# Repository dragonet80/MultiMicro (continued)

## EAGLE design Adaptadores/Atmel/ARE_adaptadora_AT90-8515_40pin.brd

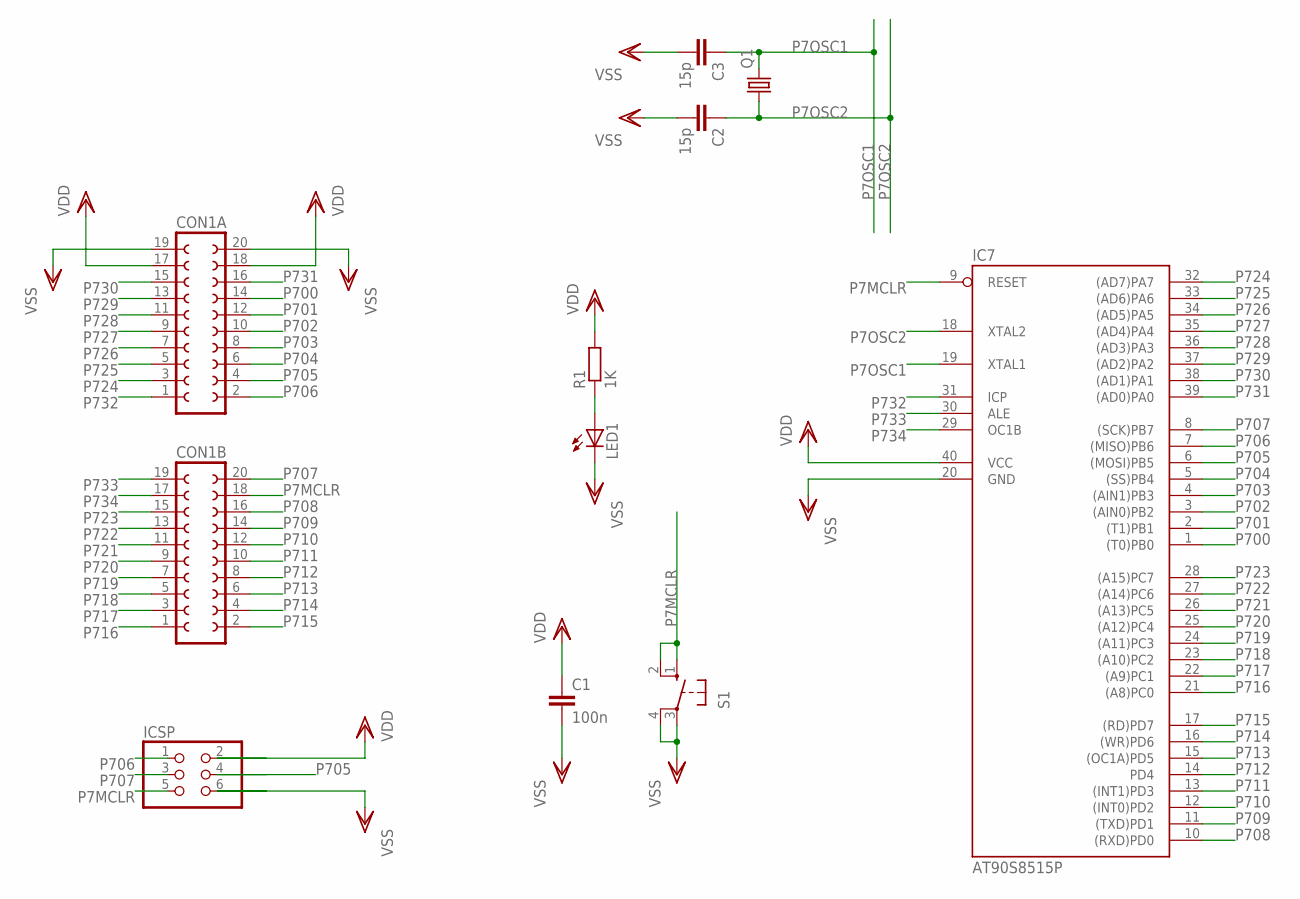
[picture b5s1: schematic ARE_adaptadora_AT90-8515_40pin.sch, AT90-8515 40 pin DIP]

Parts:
C1: 100n; C0805
C2, C3: 15p; C0805
CON1A, CON1B: FE10-2W
IC7: AT90S8515P; DIL40
ICSP: PINHD-2X3; 2X03
LED1: LED3MM
Q1: CRYSTALHC18U-V; HC18U-V
R1: 1K; R0805
S1: 10-XX; B3F-10XX; MPN B3F-1000

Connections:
unnamed: LED1.A, R1.1
P7MCLR: CON1B.18, IC7.9 (RESET), ICSP.5, S1.1 (S), S1.2 (S1)
P7OSC1: C3.1, IC7.19 (XTAL1), Q1.2
P7OSC2: C2.1, IC7.18 (XTAL2), Q1.1
P700: CON1A.14, IC7.1 ((T0)PB0)
P701: CON1A.12, IC7.2 ((T1)PB1)
P702: CON1A.10, IC7.3 ((AIN0)PB2)
P703: CON1A.8, IC7.4 ((AIN1)PB3)
P704: CON1A.6, IC7.5 ((SS)PB4)
P705: CON1A.4, IC7.6 ((MOSI)PB5), ICSP.4
P706: CON1A.2, IC7.7 ((MISO)PB6), ICSP.1
P707: CON1B.20, IC7.8 ((SCK)PB7), ICSP.3
P708: CON1B.16, IC7.10 ((RXD)PD0)
P709: CON1B.14, IC7.11 ((TXD)PD1)
P710: CON1B.12, IC7.12 ((INT0)PD2)
P711: CON1B.10, IC7.13 ((INT1)PD3)
P712: CON1B.8, IC7.14 (PD4)
P713: CON1B.6, IC7.15 ((OC1A)PD5)
P714: CON1B.4, IC7.16 ((WR)PD6)
P715: CON1B.2, IC7.17 ((RD)PD7)
P716: CON1B.1, IC7.21 ((A8)PC0)
P717: CON1B.3, IC7.22 ((A9)PC1)
P718: CON1B.5, IC7.23 ((A10)PC2)
P719: CON1B.7, IC7.24 ((A11)PC3)
P720: CON1B.9, IC7.25 ((A12)PC4)
P721: CON1B.11, IC7.26 ((A13)PC5)
P722: CON1B.13, IC7.27 ((A14)PC6)
P723: CON1B.15, IC7.28 ((A15)PC7)
P724: CON1A.3, IC7.32 ((AD7)PA7)
P725: CON1A.5, IC7.33 ((AD6)PA6)
P726: CON1A.7, IC7.34 ((AD5)PA5)
P727: CON1A.9, IC7.35 ((AD4)PA4)
P728: CON1A.11, IC7.36 ((AD3)PA3)
P729: CON1A.13, IC7.37 ((AD2)PA2)
P730: CON1A.15, IC7.38 ((AD1)PA1)
P731: CON1A.16, IC7.39 ((AD0)PA0)
P732: CON1A.1, IC7.31 (ICP)
P733: CON1B.19, IC7.30 (ALE)
P734: CON1B.17, IC7.29 (OC1B)
VDD: C1.1, CON1A.17, CON1A.18, IC7.40 (VCC), ICSP.2, R1.2
VSS: C1.2, C2.2, C3.2, CON1A.19, CON1A.20, IC7.20 (GND), ICSP.6, LED1.K (C), S1.3, S1.4 (P1)

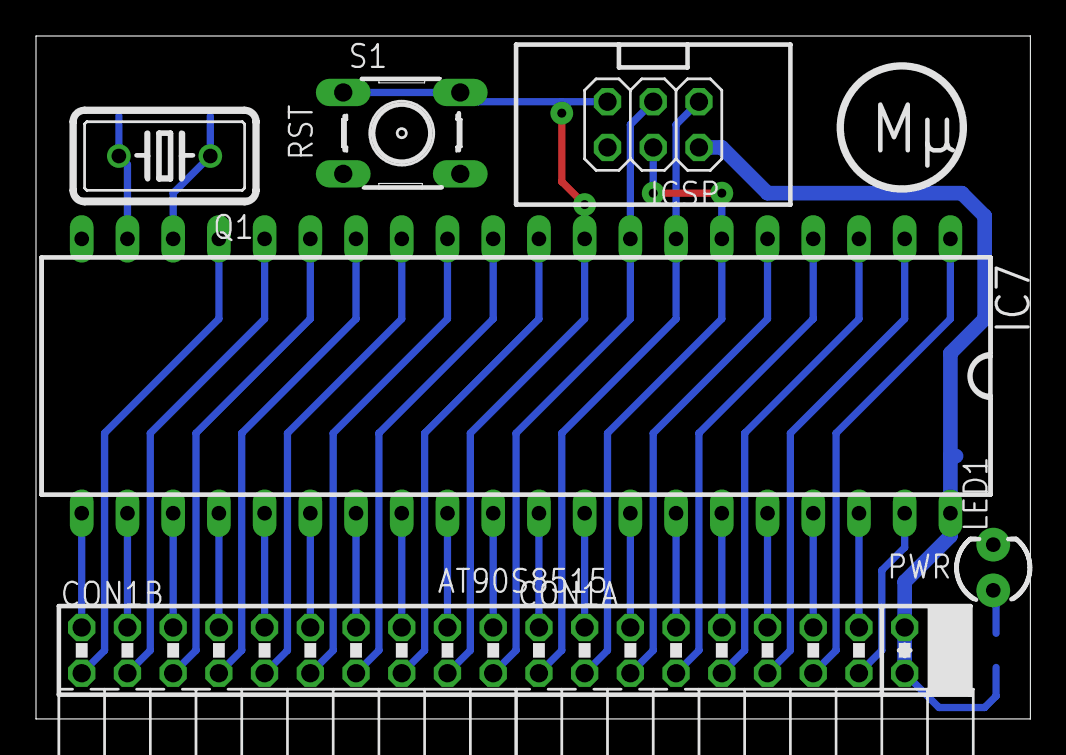
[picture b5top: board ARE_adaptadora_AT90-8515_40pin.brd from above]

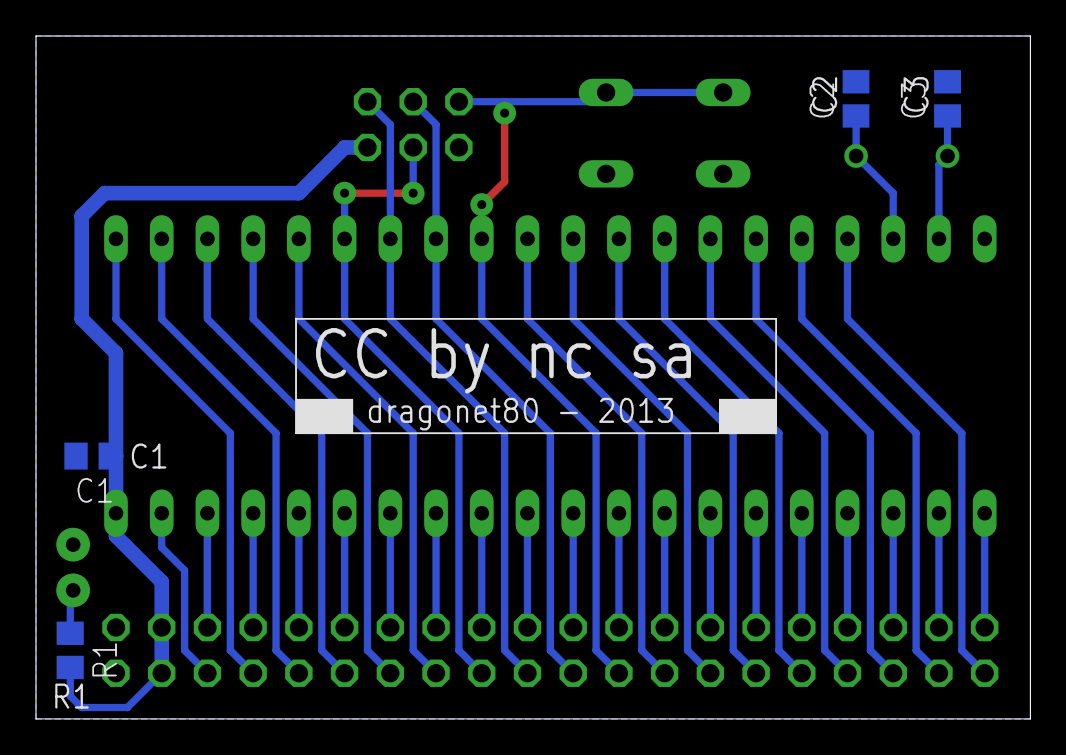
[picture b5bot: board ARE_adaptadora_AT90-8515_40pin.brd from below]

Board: 2 copper layers, 55.2 x 37.9 mm, 11 parts (4 on the bottom side), 41 nets.

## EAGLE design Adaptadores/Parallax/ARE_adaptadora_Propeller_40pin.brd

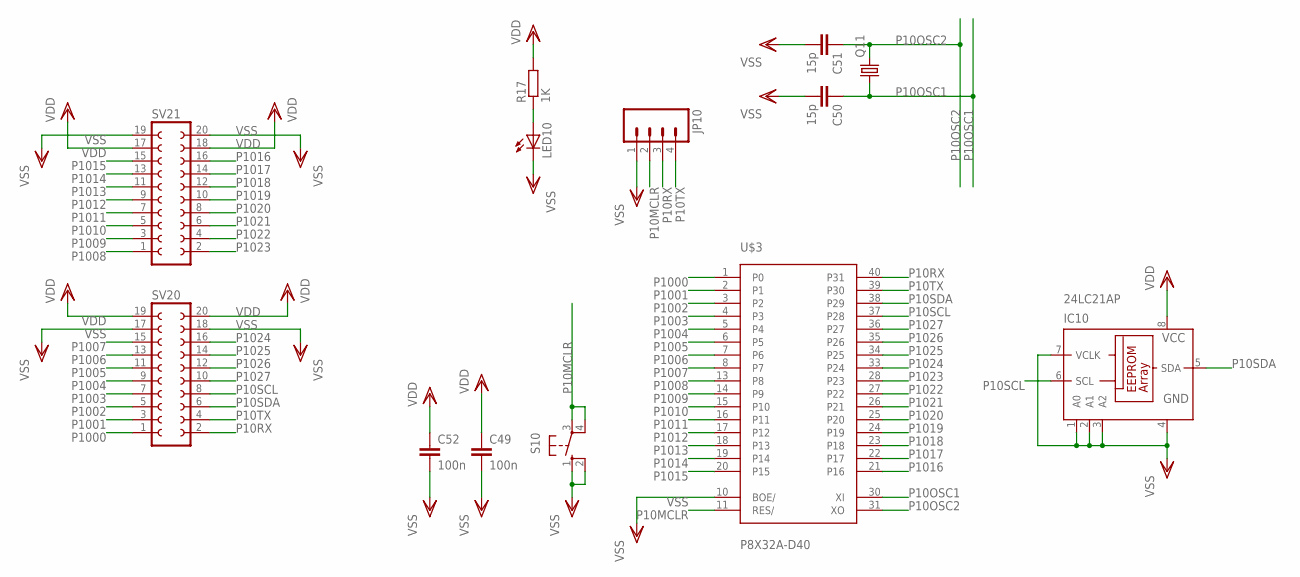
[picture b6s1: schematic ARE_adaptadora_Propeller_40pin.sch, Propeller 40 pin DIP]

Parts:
C49, C52: 100n; C0805
C50, C51: 15p; C0805
IC10: 24LC21AP; DIL8
JP10: M04PTH; 1X04
LED10: LED3MM
Q11: CRYSTALHC18U-V; HC18U-V
R17: 1K; R0805
S10: 10-XX; B3F-10XX; MPN B3F-1000
SV20, SV21: FE10-2W
U$3: P8X32A-D40

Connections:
unnamed: LED10.A, R17.1
P10MCLR: JP10.2, S10.3, S10.4 (P1), U$3.11 (RES/)
P10OSC1: C50.1, Q11.1, U$3.30 (XI)
P10OSC2: C51.1, Q11.2, U$3.31 (XO)
P10RX: JP10.3, SV20.2, U$3.40 (P31)
P10SCL: IC10.6 (SCL), SV20.8, U$3.37 (P28)
P10SDA: IC10.5 (SDA), SV20.6, U$3.38 (P29)
P10TX: JP10.4, SV20.4, U$3.39 (P30)
P1000: SV20.1, U$3.1 (P0)
P1001: SV20.3, U$3.2 (P1)
P1002: SV20.5, U$3.3 (P2)
P1003: SV20.7, U$3.4 (P3)
P1004: SV20.9, U$3.5 (P4)
P1005: SV20.11, U$3.6 (P5)
P1006: SV20.13, U$3.7 (P6)
P1007: SV20.15, U$3.8 (P7)
P1008: SV21.1, U$3.13 (P8)
P1009: SV21.3, U$3.14 (P9)
P1010: SV21.5, U$3.15 (P10)
P1011: SV21.7, U$3.16 (P11)
P1012: SV21.9, U$3.17 (P12)
P1013: SV21.11, U$3.18 (P13)
P1014: SV21.13, U$3.19 (P14)
P1015: SV21.15, U$3.20 (P15)
P1016: SV21.16, U$3.21 (P16)
P1017: SV21.14, U$3.22 (P17)
P1018: SV21.12, U$3.23 (P18)
P1019: SV21.10, U$3.24 (P19)
P1020: SV21.8, U$3.25 (P20)
P1021: SV21.6, U$3.26 (P21)
P1022: SV21.4, U$3.27 (P22)
P1023: SV21.2, U$3.28 (P23)
P1024: SV20.16, U$3.33 (P24)
P1025: SV20.14, U$3.34 (P25)
P1026: SV20.12, U$3.35 (P26)
P1027: SV20.10, U$3.36 (P27)
VDD: C49.1, C52.1, IC10.8 (VCC), R17.2, SV20.19, SV20.20, SV21.17, SV21.18, U$3.12 (VDD), U$3.32 (VDD)
VSS: C49.2, C50.2, C51.2, C52.2, IC10.1 (A0), IC10.2 (A1), IC10.3 (A2), IC10.4 (GND), IC10.7 (VCLK), JP10.1, LED10.K (C), S10.1 (S), S10.2 (S1), SV20.17, SV20.18, SV21.19, SV21.20, U$3.9 (VSS), U$3.10 (BOE/), U$3.29 (VSS)

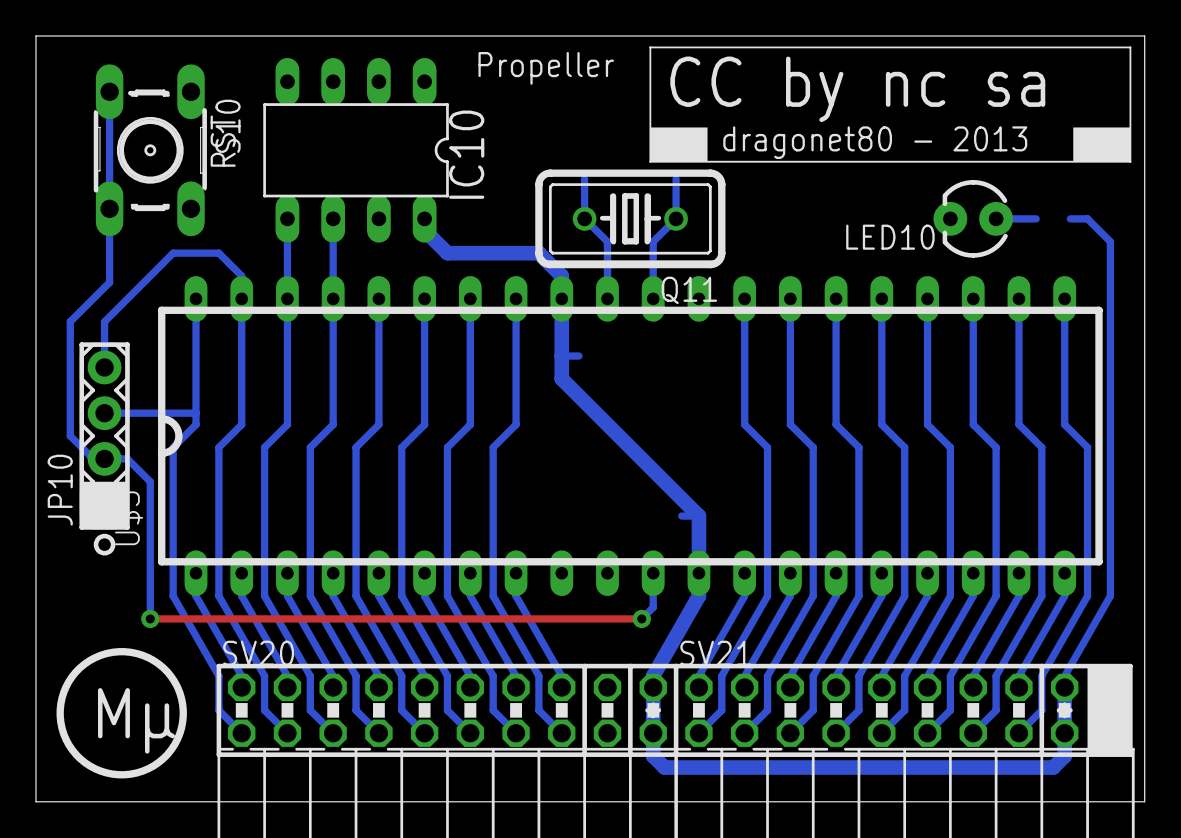
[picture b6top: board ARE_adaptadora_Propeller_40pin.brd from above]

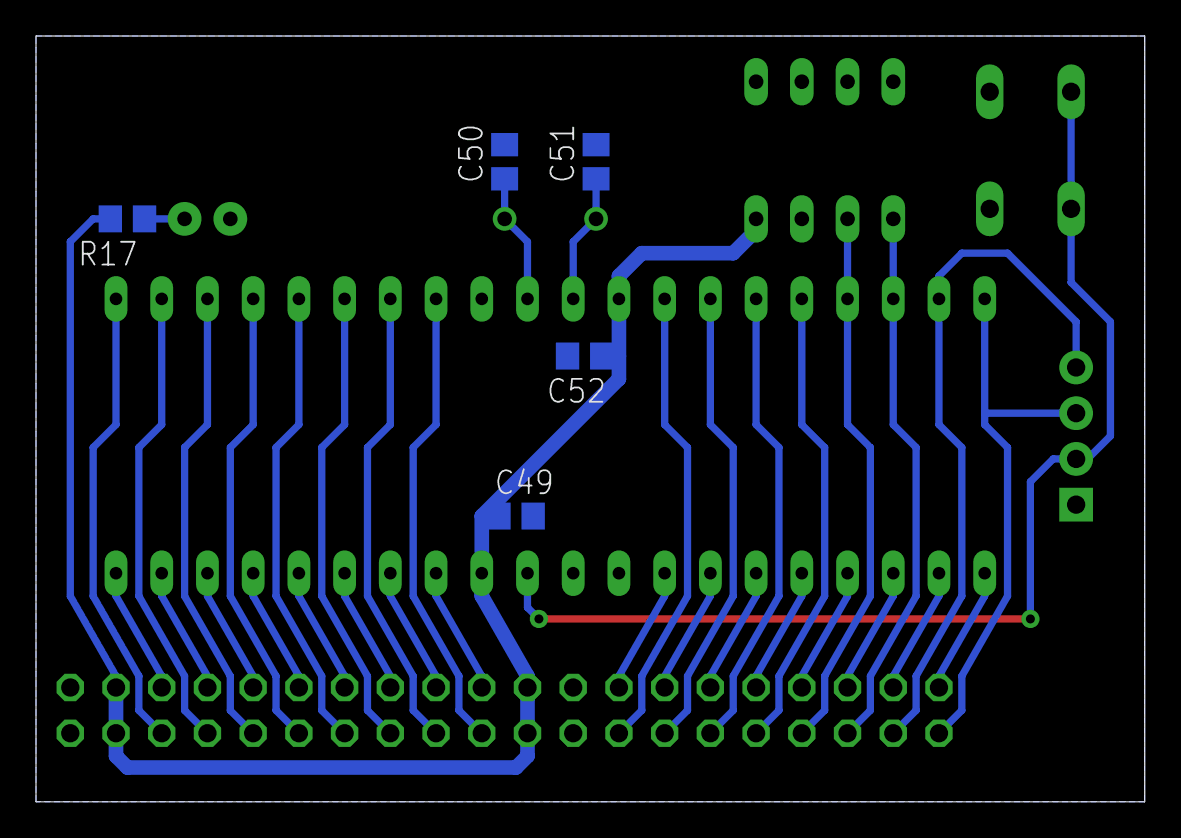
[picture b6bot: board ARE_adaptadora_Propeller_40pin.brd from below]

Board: 2 copper layers, 61.6 x 42.5 mm, 13 parts (5 on the bottom side), 38 nets.

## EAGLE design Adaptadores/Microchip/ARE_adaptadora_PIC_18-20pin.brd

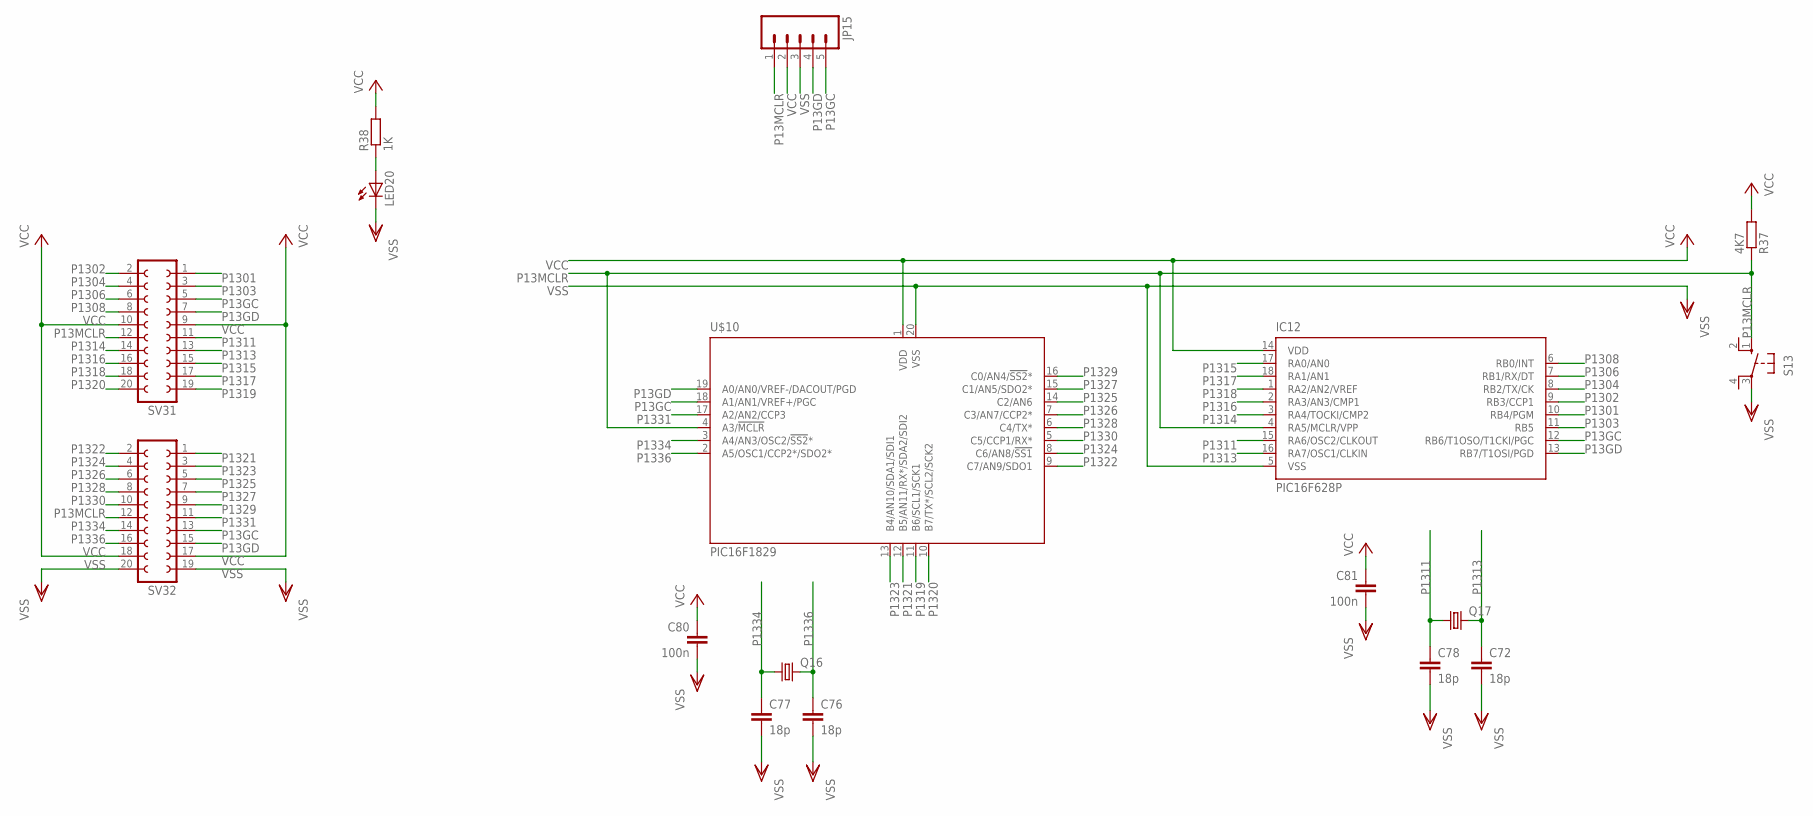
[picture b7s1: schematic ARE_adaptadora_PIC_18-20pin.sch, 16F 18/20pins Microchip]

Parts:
C72, C76, C77, C78: 18p; C0805
C80, C81: 100n; C0805
IC12: PIC16F628P; DIL18
JP15: M05PTH; 1X05
LED20: LEDCHIPLED_0805; CHIPLED_0805
Q16, Q17: CRYSTALHC18U-V; HC18U-V
R37: 4K7; R0805
R38: 1K; R0805
S13: 10-XX; B3F-10XX; MPN B3F-1000
SV31, SV32: FE10-2W
U$10: PIC16F1829; DIL20

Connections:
unnamed: LED20.A, R38.1
P13GC: IC12.12 (RB6/T1OSO/T1CKI/PGC), JP15.5, SV31.5, SV32.13, U$10.18 (A1/AN1/VREF+/PGC)
P13GD: IC12.13 (RB7/T1OSI/PGD), JP15.4, SV31.7, SV32.15, U$10.19 (A0/AN0/VREF-/DACOUT/PGD)
P13MCLR: IC12.4 (RA5/MCLR/VPP), JP15.1, R37.1, S13.1 (S), SV31.12, SV32.12, U$10.4 (A3/!MCLR)
P1301: IC12.10 (RB4/PGM), SV31.1
P1302: IC12.9 (RB3/CCP1), SV31.2
P1303: IC12.11 (RB5), SV31.3
P1304: IC12.8 (RB2/TX/CK), SV31.4
P1306: IC12.7 (RB1/RX/DT), SV31.6
P1308: IC12.6 (RB0/INT), SV31.8
P1311: C78.1, IC12.15 (RA6/OSC2/CLKOUT), Q17.1, SV31.11
P1313: C72.1, IC12.16 (RA7/OSC1/CLKIN), Q17.2, SV31.13
P1314: IC12.3 (RA4/TOCKI/CMP2), SV31.14
P1315: IC12.17 (RA0/AN0), SV31.15
P1316: IC12.2 (RA3/AN3/CMP1), SV31.16
P1317: IC12.18 (RA1/AN1), SV31.17
P1318: IC12.1 (RA2/AN2/VREF), SV31.18
P1319: SV31.19, U$10.11 (B6/SCL1/SCK1)
P1320: SV31.20, U$10.10 (B7/TX*/SCL2/SCK2)
P1321: SV32.1, U$10.12 (B5/AN11/RX*/SDA2/SDI2)
P1322: SV32.2, U$10.9 (C7/AN9/SDO1)
P1323: SV32.3, U$10.13 (B4/AN10/SDA1/SDI1)
P1324: SV32.4, U$10.8 (C6/AN8/!SS1)
P1325: SV32.5, U$10.14 (C2/AN6)
P1326: SV32.6, U$10.7 (C3/AN7/CCP2*)
P1327: SV32.7, U$10.15 (C1/AN5/SDO2*)
P1328: SV32.8, U$10.6 (C4/TX*)
P1329: SV32.9, U$10.16 (C0/AN4/!SS2!*)
P1330: SV32.10, U$10.5 (C5/CCP1/RX*)
P1331: SV32.11, U$10.17 (A2/AN2/CCP3)
P1334: C77.1, Q16.1, SV32.14, U$10.3 (A4/AN3/OSC2/!SS2!*)
P1336: C76.1, Q16.2, SV32.16, U$10.2 (A5/OSC1/CCP2*/SDO2*)
VCC: C80.1, C81.1, IC12.14 (VDD), JP15.2, R37.2, R38.2, SV31.9, SV31.10, SV32.17, SV32.18, U$10.1 (VDD)
VSS: C72.2, C76.2, C77.2, C78.2, C80.2, C81.2, IC12.5 (VSS), JP15.3, LED20.C, S13.3, SV32.19, SV32.20, U$10.20 (VSS)

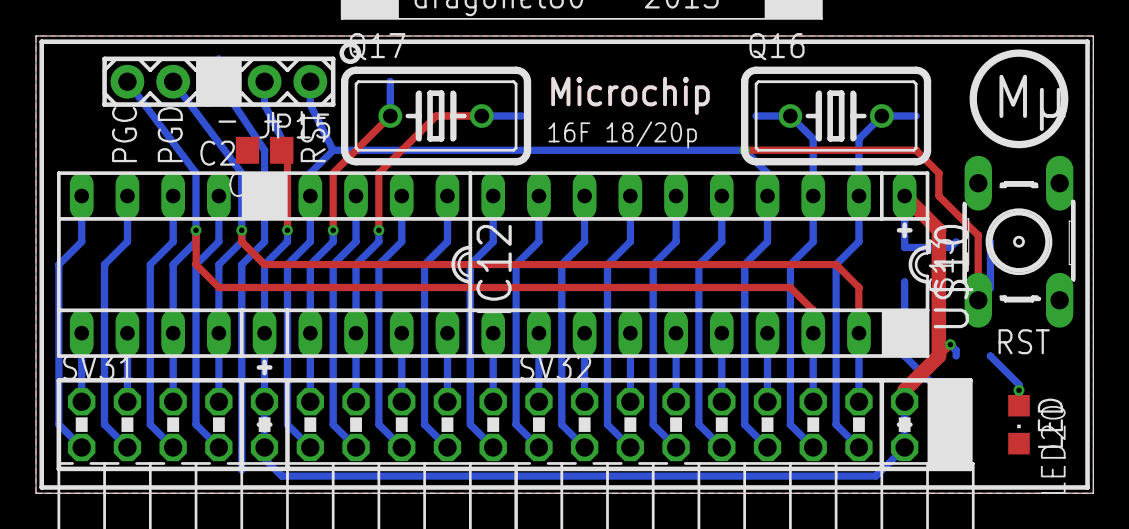
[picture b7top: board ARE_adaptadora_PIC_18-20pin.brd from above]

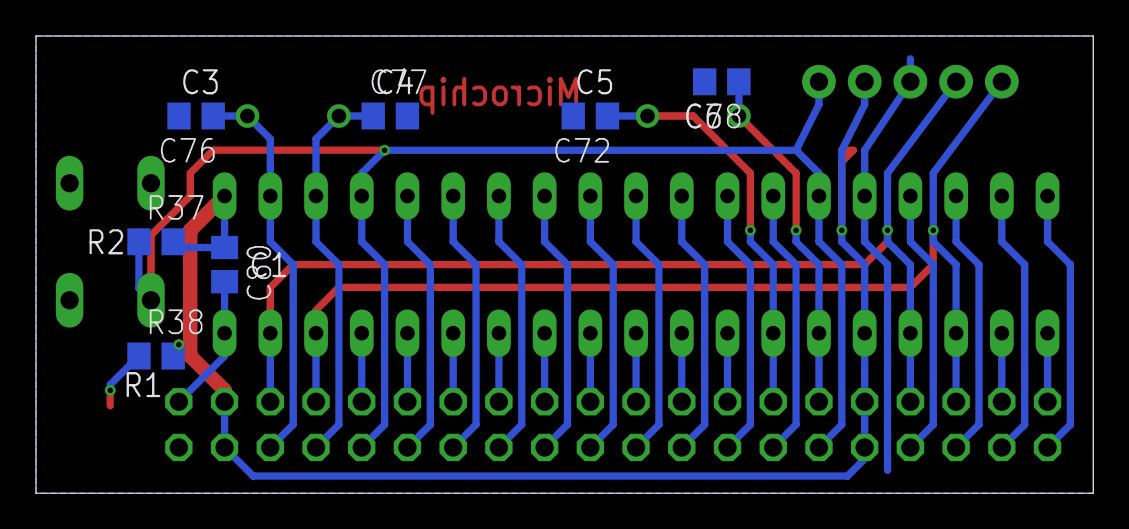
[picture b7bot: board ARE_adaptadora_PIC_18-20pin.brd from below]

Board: 2 copper layers, 58.7 x 25.4 mm, 17 parts (7 on the bottom side), 34 nets.

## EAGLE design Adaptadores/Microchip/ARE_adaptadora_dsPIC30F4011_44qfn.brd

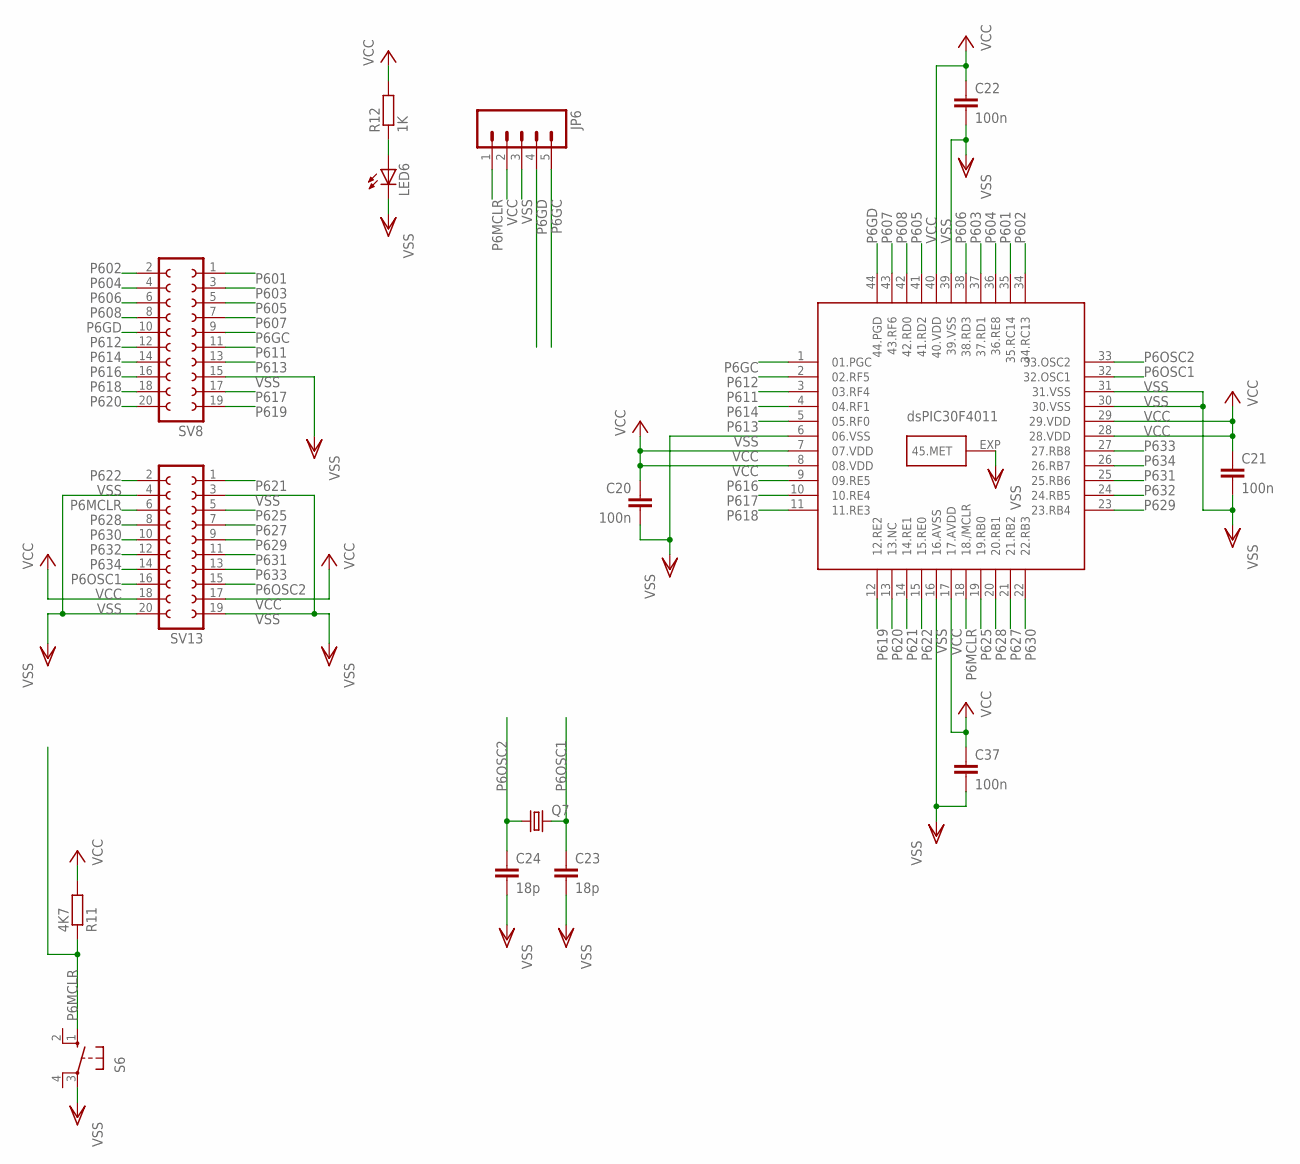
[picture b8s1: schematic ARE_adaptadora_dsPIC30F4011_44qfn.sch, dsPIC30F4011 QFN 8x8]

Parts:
C20, C21, C22, C37: 100n; C0805
C23, C24: 18p; C0805
JP6: M05PTH; 1X05
LED6: LEDCHIPLED_0805; CHIPLED_0805
Q7: CRYSTALHC18U-V; HC18U-V
R11: 4K7; R0805
R12: 1K; R0805
S6: 10-XX; B3F-10XX; MPN B3F-1000
SV8, SV13: FE10-2W
U$2: DSPIC30F4011; QFN44ML8X8

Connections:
unnamed: LED6.A, R12.1
P6GC: JP6.5, SV8.9, U$2.1 (01.PGC)
P6GD: JP6.4, SV8.10, U$2.44 (44.PGD)
P6MCLR: JP6.1, R11.1, S6.1 (S), SV13.6, U$2.18 (18./MCLR)
P6OSC1: C23.1, Q7.2, SV13.16, U$2.32 (32.OSC1)
P6OSC2: C24.1, Q7.1, SV13.15, U$2.33 (33.OSC2)
P601: SV8.1, U$2.35 (35.RC14)
P602: SV8.2, U$2.34 (34.RC13)
P603: SV8.3, U$2.37 (37.RD1)
P604: SV8.4, U$2.36 (36.RE8)
P605: SV8.5, U$2.41 (41.RD2)
P606: SV8.6, U$2.38 (38.RD3)
P607: SV8.7, U$2.43 (43.RF6)
P608: SV8.8, U$2.42 (42.RD0)
P611: SV8.11, U$2.3 (03.RF4)
P612: SV8.12, U$2.2 (02.RF5)
P613: SV8.13, U$2.5 (05.RF0)
P614: SV8.14, U$2.4 (04.RF1)
P616: SV8.16, U$2.9 (09.RE5)
P617: SV8.17, U$2.10 (10.RE4)
P618: SV8.18, U$2.11 (11.RE3)
P619: SV8.19, U$2.12 (12.RE2)
P620: SV8.20, U$2.13 (13.NC)
P621: SV13.1, U$2.14 (14.RE1)
P622: SV13.2, U$2.15 (15.RE0)
P625: SV13.5, U$2.19 (19.RB0)
P627: SV13.7, U$2.21 (21.RB2)
P628: SV13.8, U$2.20 (20.RB1)
P629: SV13.9, U$2.23 (23.RB4)
P630: SV13.10, U$2.22 (22.RB3)
P631: SV13.11, U$2.25 (25.RB6)
P632: SV13.12, U$2.24 (24.RB5)
P633: SV13.13, U$2.27 (27.RB8)
P634: SV13.14, U$2.26 (26.RB7)
VCC: C20.1, C21.1, C22.1, C37.1, JP6.2, R11.2, R12.2, SV13.17, SV13.18, U$2.7 (07.VDD), U$2.8 (08.VDD), U$2.17 (17.AVDD), U$2.28 (28.VDD), U$2.29 (29.VDD), U$2.40 (40.VDD)
VSS: C20.2, C21.2, C22.2, C23.2, C24.2, C37.2, JP6.3, LED6.C, S6.3, SV8.15, SV13.3, SV13.4, SV13.19, SV13.20, U$2.6 (06.VSS), U$2.16 (16.AVSS), U$2.30 (30.VSS), U$2.31 (31.VSS), U$2.39 (39.VSS), U$2.EXP (45.MET)

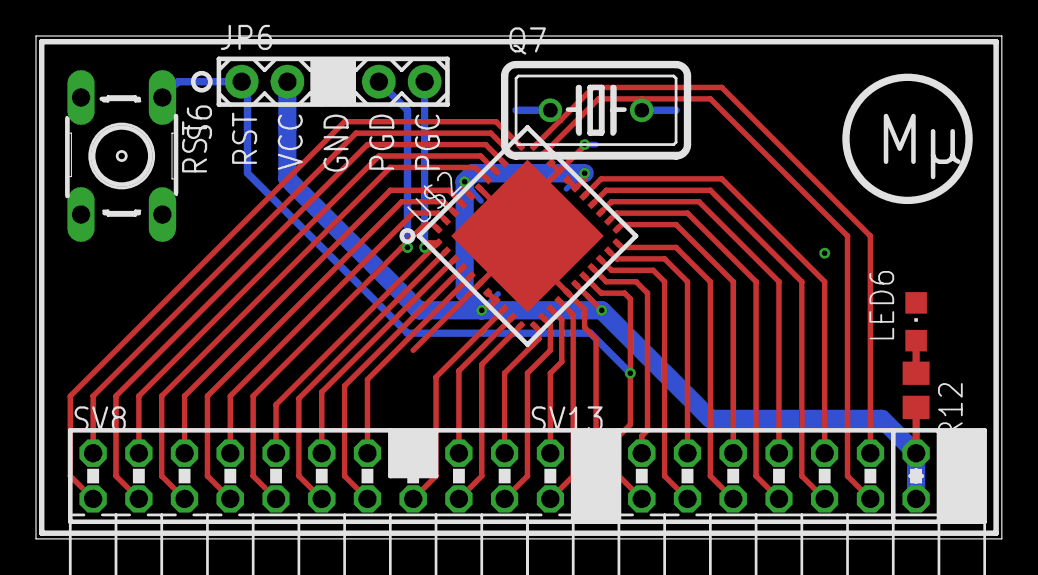
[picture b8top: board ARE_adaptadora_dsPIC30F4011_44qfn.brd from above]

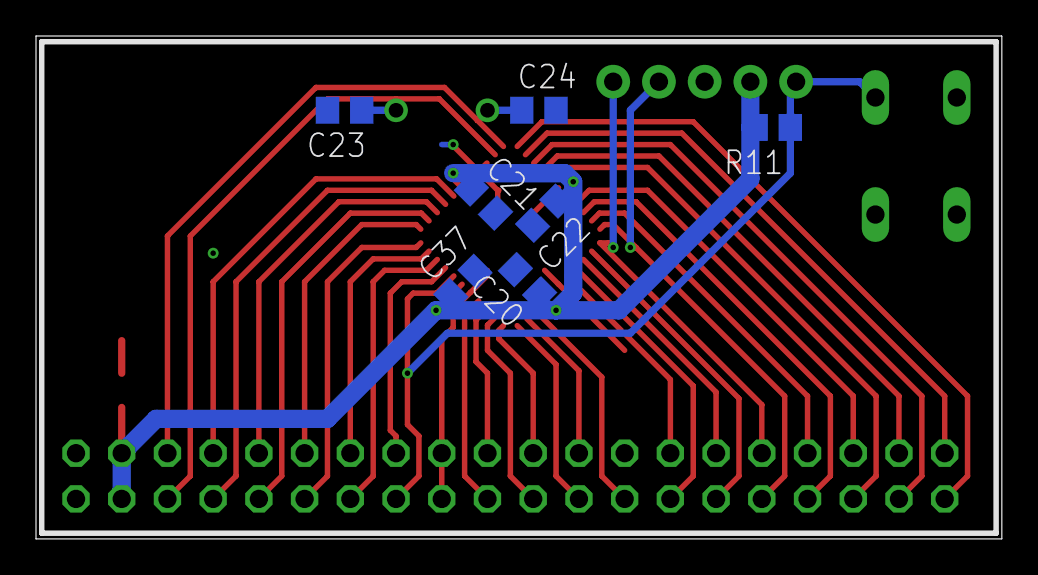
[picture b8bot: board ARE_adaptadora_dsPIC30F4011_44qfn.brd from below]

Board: 2 copper layers, 53.7 x 27.9 mm, 15 parts (7 on the bottom side), 36 nets.

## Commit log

2013-03-08 Added first batch of pcbs
    Added Base board versión 1.0
    Added first set of adapter boards for Microchip 6, 8, 14, 44 and 64
    pins.
    Added some preliminary set of add-on boards.
2013-03-08 Added component source links
    Added some of the most important links to buy the components in eBay.
2013-03-19 Added first batch of Microchip adapter pcbs
    A 10x10cm board consisting of 4 Microchip adapters:
    * 64 pin micro for PIC32, dsPIC and PIC24.
    * 44 pin micro for PIC32, dsPIC and PIC24.
    * 44 pin micro for PIC16 and PIC18.
    * 8/14 pin micro for PIC10, PIC12 and PIC16.
    Theres also a square ruler mm/inch as a bonnus.
2013-04-15 Adaptadores v1.01
    Added adapter board for this micros:
    * Microchip dsPIC30F4011 in QFN-44 format.
    * Microchip PIC32/dsPIC33 in SOIC-28 format.
    * Atmel AT908515 in DIP-40 format.
    * Atmel AT908535 in DIP-40 format.
    * Microchip PIC16/18 in DIP-40 format.
2013-04-16 Added template for pin labels
    Added a template for pin labels in .DXF format. It is still just a
    template and it those not correspond to any final adapter pcb yet. It is
    just to see the idea. I hope to have it finished soon.
2013-04-26 Added template for pin labels
    Added a template for pin labels. This one is in .XLS format (97-2003
    version) instead of .DXF. I think this is a much more convenient format
    and easier to modify, print and create new ones.
2013-05-07 Added new 64 pin version of base trainer
    * Added a new 64 pin version of base trainer. These are the changes:
    -> Reduced main connector from 3x30 to 2x30. Now it can accept
    microcontroles up to 64 pin, wich is enough for most hobbyst.
    -> Redistributed most components to gain some space. Thanks to this
    increment, now it is possible to place a full breadboard.
    -> Reduced from 8 to only 4 pushbuttons.
2015-02-18 New version and a massive re-arrengement
    New version of base trainer. Now it is called Ardu-Trainer MultiMicro,
    as it has an ATMEGA32U4 with all its pins available. It can be
    programmed with Arduino bootloader or directly with your own firmware.
    All of MultiMicro adapters have been revised, cleaned and sorted.
2015-02-18 Added STM32 adapter
    Added an STM32F4xx adapter 64 pin version.
    Also added a couple of files missing from OLD adapters.
